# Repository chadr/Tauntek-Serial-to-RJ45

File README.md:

# Tauntek Serial to RJ45
 Serial IDC to RJ45 adapter for Tauntek IC Logic Tester.

 Allows the use of a Cisco terminal cable (sometimes called a Yost cable) to connect to a Tauntek IC Logic Tester. Cisco terminal cables are DB9 to RJ45 in a rollover configuration.

The switch will swap RX and TX, if needed.

|           Item           |   Mfg Part #   |   Mouser Part #  |
|------------------------- | -------------- | ---------------- |
|AMP PCB Mount RJ45 Socket |  RJE561881410  | 523-RJE561881410 |
|  C&K DPDT Slide Switch   |  JS202011CQN   | 611-JS202011CQN  |
| Samtec 2x5 2.54mm Socket | SSQ-105-02-T-D |  200-SSQ10502TD  |

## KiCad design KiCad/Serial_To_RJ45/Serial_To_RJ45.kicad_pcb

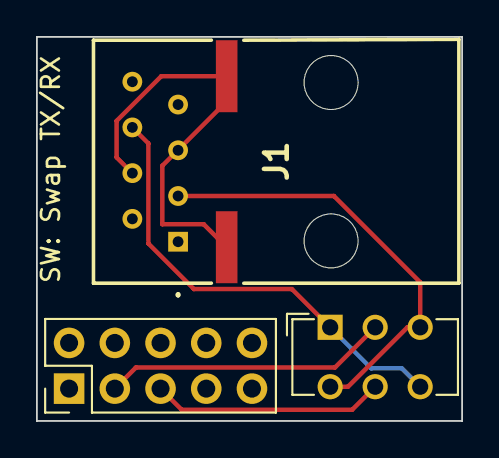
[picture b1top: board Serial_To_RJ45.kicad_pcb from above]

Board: 2 copper layers, 23.6 x 21.3 mm, 3 parts (0 on the bottom side), 5 nets.

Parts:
J1: RJE561881410
J2: Serial IDC Header; PinHeader_2x05_P2.54mm_Vertical
SW: Swap TX/RX: SW_DPDT_x2; SW_CuK_JS202011CQN_DPDT_Straight

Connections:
/RXD: J1.6, SW: Swap TX/RX.1 (A), SW: Swap TX/RX.6 (C)
/TXD: J1.3, SW: Swap TX/RX.3 (C), SW: Swap TX/RX.4 (A)
GND: J1.4, J1.5, J1.G1 (GROUND_1), J1.G2 (GROUND_2), J2.9
unnamed: J2.3, SW: Swap TX/RX.2 (B)
unnamed: J2.5, SW: Swap TX/RX.5 (B)

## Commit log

2023-11-14 Added Switch for RX TX
2023-11-15 upload schematic pdf
